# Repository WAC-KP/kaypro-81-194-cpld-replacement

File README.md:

# Kaypro 81-194 cpld replacement
Replacement for the 1984 Kaypro Universal Board 81-194 LSI using an ATF1504 CPLD, AS6C1008 SRAM and 16 mHz oscillator.

## License

This project is licensed under the **GNU General Public License v3.0 (GPLv3)**. 

### What this means for the community:
- **You are free** to download, build, modify, and use these schematics, Gerbers, and CPLD code for your own Kaypro computers.
- **You can manufacture** these replacement boards for yourself or sell them to other hobbyists.
- **CRITICAL CONDITION:** If you modify the CPLD code or the PCB layout and choose to distribute or sell your new version, **you are legally required to make your modified source code and hardware design files publicly available** under this exact same GPLv3 license. 

For the full legal text, see the accompanying `LICENSE` file.

## Why this project

A while back I purchased a nonworking Kaypro 2x as a parts computer. It was dirty and many of the screws were rusting. The keyboard jack was broken. The power supply was broken (literally). Otherwise everything else looked good. Comparison to a working 2x revealed a few bad RAM chips and the corrupted 81-194 LSI. Replacing the faulty ram and borrowing a working 81-194 resulted in a fully functional Kaypro 2X. 

A web search revealed no viable solutions to the dead LSI chip. So I asked AI for help. At the suggestion (urging) of AI and to simplify code, the design moved away from RAM to SRAM. The end result was a working, stable Kaypro 2x. 

Was it worth it? Perhaps, perhaps not. You can still find universal board Kaypros, working or not. Prototype PCBs are not too expensive until you add in shipping. Parts are reasonable but all combined you might just get lucky and find another Kaypro for less than the parts and labor.

That said, I believe it was worth it, simply based on the learning process and the side result of a functional Kaypro.

## Downloads & Project Files

Instead of hunting through folders, you can access the core design files for this project directly using the links below:

### 🛠️ Hardware & PCB Fabrication
* **Schematic Diagram:** [View or Download Schematic PDF](hardware/Version%201/u29-1504.pdf)
* **Gerber Files V1:** [Download V1 PCB Fabrication ZIP](hardware/Version%201/production/u29-1504.zip)
* **Gerber Files V2:** [Download V2 PCB Fabrication ZIP](hardware/Version%202/production/u29-1504.zip)
* *Note: The Gerber ZIP file can be uploaded directly to manufacturing services like JLCPCB, PCBWay, or OSH Park. Version 2 is just a repositioning of components.

### 💾 Firmware & Source Code
* **CPLD Source Code:** [ATF1504 PLD Source Code](firmware/KAYPRO_SRAM_CTRL-6.pld)
* **Compiled JEDEC File:** [Ready-to-Program JED file](firmware/KAYPRO_SRAM_CTRL-6.jed)
* **Compiled svf File:** [Ready-to-Program svf file](firmware/KAYPRO_SRAM_CTRL-6.svf)
* *Note: Use the `.jed` file directly with your USB Blaster and the ATF15xx ISP software to program the chip.*
* *Note: Use the `.svf` file directly with your modified USB Blaster Clone and UrJTAG or OpenOCD software to program the chip.*

---

### Brief notes

* The PCB is designed to replace both U29 (81-194) and U55 (74LS373). Separate the PCB into the two daughter boards and mount the components. The two boards are connected by a 16 wire ribbon cable.
* A single RST connection is provided (see the PCB)
* To minimize risk of socket damage only use rounded header pins designed for interfacing with DIP sockets. 
* 0805 surface mount capacitors and resistors are used to help reduce clutter and they can still be hand soldered. 
* External power pins can be used to supply the required 5v for programming the CPLD or the CPLD can be programmed with the board installed. 
* A heartbeat LED is provided as a visual indicator of functioning AFT1504.
* Remove all RAM chips. Remove U55. Remove failed 81-194 (U29)

### Compiling pld with WinCUPL II
 &emsp;cupl.exe -m1l -age -b -u PATH_TO\atmel.lib KAYPRO_SRAM_CTRL-6.pld  
 &emsp;fit1504.exe KAYPRO_SRAM_CTRL-6.tt2 -device PLCC44 -preassign keep -jtag on  

### Programming ATF1504AS with UrJtag
 &emsp;run JTAG  
  &emsp;&emsp;jtag> cable usbblaster  
  &emsp;&emsp;jtag> detect  
  &emsp;&emsp;jtag> part 0  
  &emsp;&emsp;jtag> instruction length 10  
  &emsp;&emsp;jtag> svf PATH_TO/KAYPRO_SRAM_CTRL-6.svf  
  &emsp;&emsp;&emsp;(programming may take a few minutes)

---  

### Resources
 - [USB Blaster Clone rev, C](https://www.amazon.com/dp/B07F5H5LPZ).
     - [Fixing a knockoff Altera USB Blaster that never worked](https://www.downtowndougbrown.com/2024/06/fixing-a-knockoff-altera-usb-blaster-that-never-worked/)
     - [Firmware binary file](https://github.com/dsm/USB-Blaster_CH552)
     - [WCHISPStudio](https://www.wch-ic.com/download/file?id=196)
 - [Microchip WinCUPL Product Page](https://www.microchip.com/en-us/development-tool/wincupl)
 - [ATMISP 7.3.1 Download (ZIP)](https://ww1.microchip.com/downloads/aemDocuments/documents/MPD/SoftwareLibrary/ATMISP_v7_3_1.zip)
 - [UrJTAG](https://urjtag.sourceforge.io/)
 - [OpenOCD](https://openocd.org/)

 <br>

Prototype Installed - forgive the oversized cable connectors. Rubber spacers stabilize the boards when cover installed.

<br><br>

## ⚠️ Kaypro Hardware & Installation Disclaimer

**CRITICAL WARNING:** This project involves modifying vintage computing equipment by directly interfacing with IC sockets. Incorrect installation or software faults can permanently destroy period-hard-to-find chips and logic boards. Use this software and hardware at your own risk.

In addition to the terms outlined in the GNU General Public License v3.0 (GPL-3.0):

* **Socket Interfacing Risk:** This software/hardware is designed to interface specifically with DIP sockets **U29** and **U55** on the **Kaypro Universal Board**. You assume all risk for incorrect orientation, bent pins, misaligned rows, or plugging into incorrect IC locations.
* **Electrical & Component Damage:** The authors and contributors shall not be held liable for any direct or indirect damage to your Kaypro mainboard, power supply (including original astec/riffa capacitors), CRT circuitry, or vintage components resulting from data corruption, improper timing signals, or logic states generated by this software.
* **Verification Required:** Ensure your board layout matches the Kaypro Universal Board configuration (e.g., Kaypro 2X, 4/84, 10) and verify all voltages before powering on the machine with this modification installed.

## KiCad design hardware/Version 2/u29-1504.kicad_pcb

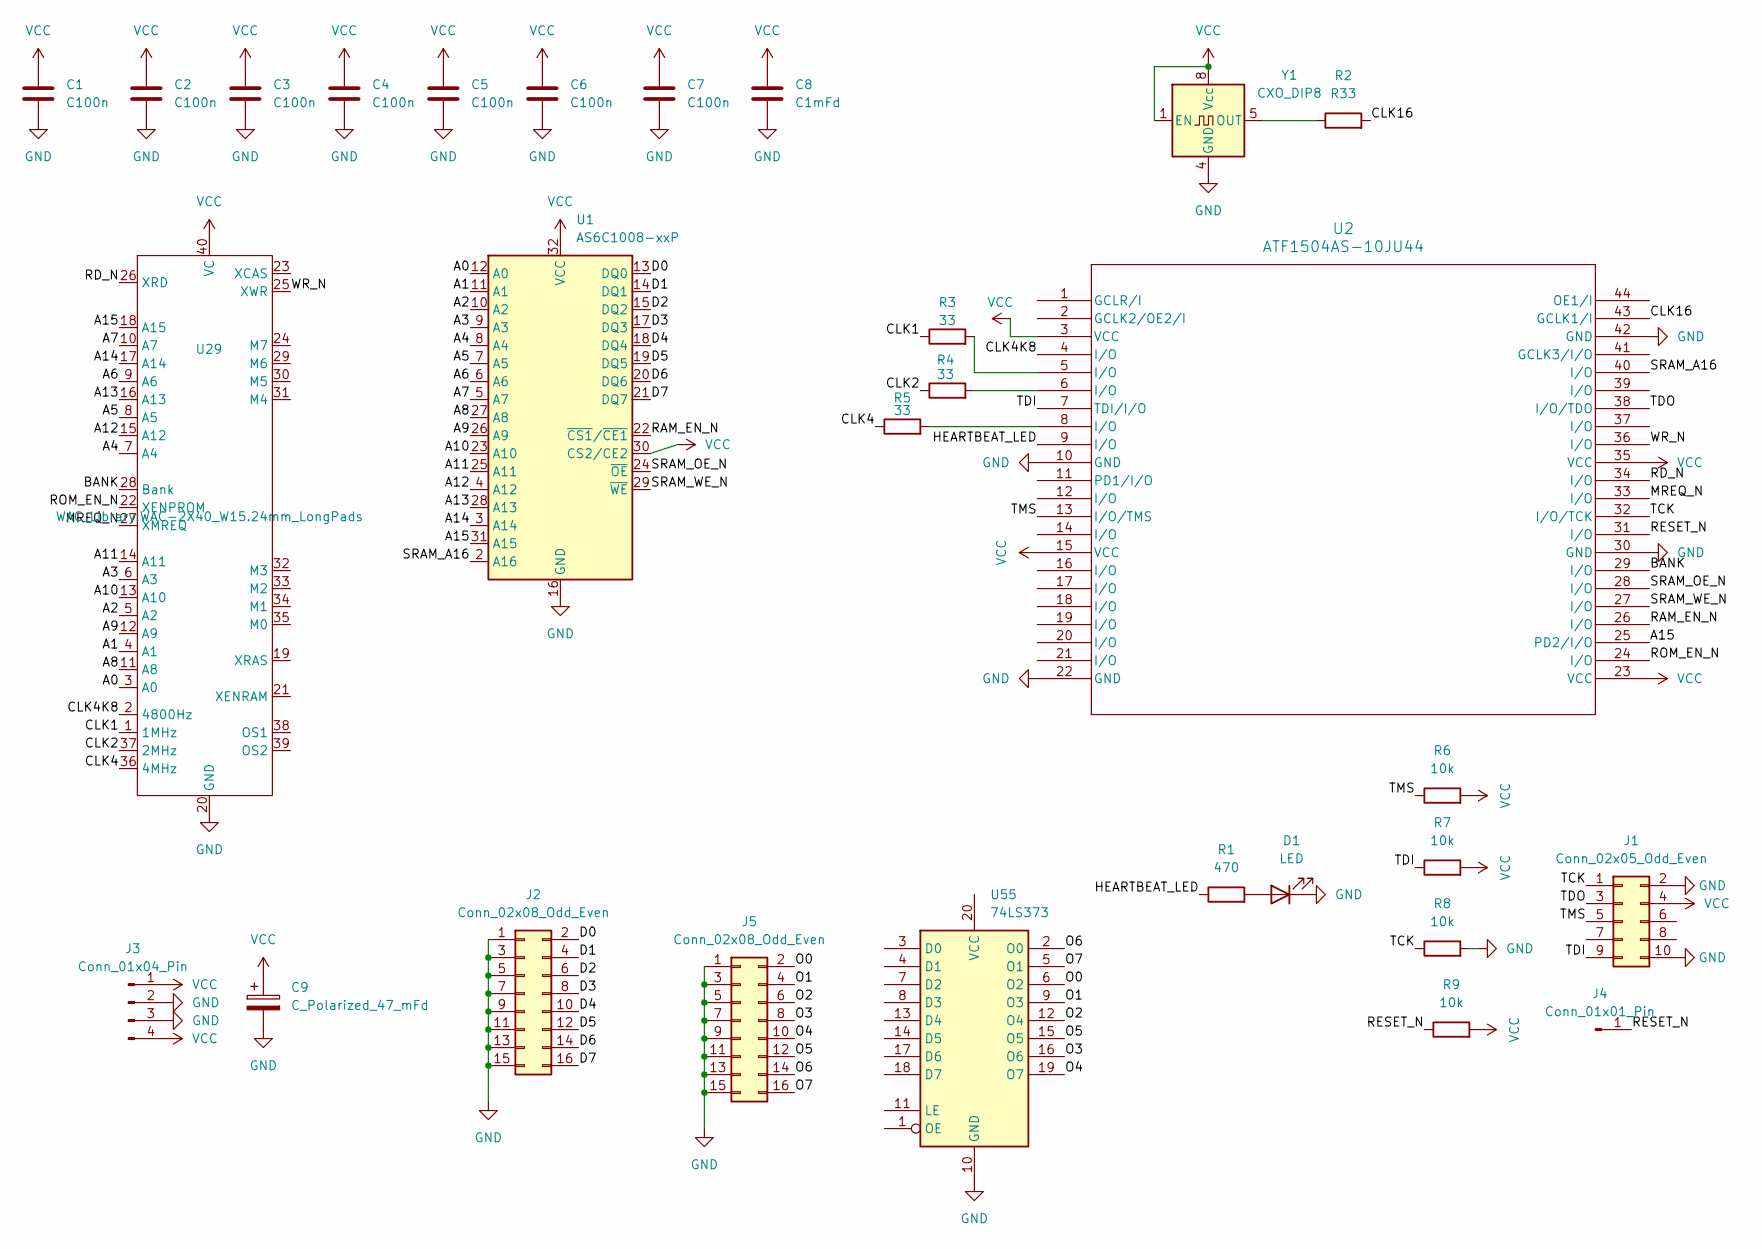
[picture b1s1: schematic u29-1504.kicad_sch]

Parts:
C1, C2, C3, C4, C5, C6, C7: C100n; C_0805_2012Metric_Pad1.18x1.45mm_HandSolder
C8: C1mFd; C_0805_2012Metric_Pad1.18x1.45mm_HandSolder
C9: C_Polarized_47_mFd; CP_Radial_D5.0mm_P2.00mm
D1: LED; LED_D3.0mm
J1: Conn_02x05_Odd_Even; IDC-Header_2x05_P2.54mm_Vertical
J2, J5: Conn_02x08_Odd_Even; PinHeader_2x08_P2.54mm_Vertical
J3: Conn_01x04_Pin; PinHeader_1x04_P2.54mm_Vertical
J4: Conn_01x01_Pin; PinHeader_1x01_P2.54mm_Vertical
R1: 470; R_0805_2012Metric_Pad1.20x1.40mm_HandSolder
R2: R33; R_0805_2012Metric_Pad1.20x1.40mm_HandSolder
R3, R4, R5: 33; R_0805_2012Metric_Pad1.20x1.40mm_HandSolder
R6, R7, R8, R9: 10k; R_0805_2012Metric_Pad1.20x1.40mm_HandSolder
U1: AS6C1008-xxP; DIP-32_W15.24mm
U2: ATF1504AS-10JU44; PLCC-44_THT-Socket
U29: Replacemnt; WAC-2X40_W15.24mm_LongPads
U55: 74LS373; DIP-20_W7.62mm
Y1: CXO_DIP8; Oscillator_DIP-8

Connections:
/A0: U1.12 (A0), U29.3 (A0)
/A1: U1.11 (A1), U29.4 (A1)
/A2: U1.10 (A2), U29.5 (A2)
/A3: U1.9 (A3), U29.6 (A3)
/A4: U1.8 (A4), U29.7 (A4)
/A5: U1.7 (A5), U29.8 (A5)
/A6: U1.6 (A6), U29.9 (A6)
/A7: U1.5 (A7), U29.10 (A7)
/A8: U1.27 (A8), U29.11 (A8)
/A9: U1.26 (A9), U29.12 (A9)
/A10: U1.23 (A10), U29.13 (A10)
/A11: U1.25 (A11), U29.14 (A11)
/A12: U1.4 (A12), U29.15 (A12)
/A13: U1.28 (A13), U29.16 (A13)
/A14: U1.3 (A14), U29.17 (A14)
/A15: U1.31 (A15), U2.25 (PD2/I/O), U29.18 (A15)
/BANK: U2.29 (I/O), U29.28 (Bank)
/CLK1: R3.1, U29.1 (1MHz)
/CLK2: R4.1, U29.37 (2MHz)
/CLK4: R5.1, U29.36 (4MHz)
/CLK4K8: U2.4 (I/O), U29.2 (4800Hz)
/CLK16: R2.2, U2.43 (GCLK1/I)
/D0: J2.2, U1.13 (DQ0)
/D1: J2.4, U1.14 (DQ1)
/D2: J2.6, U1.15 (DQ2)
/D3: J2.8, U1.17 (DQ3)
/D4: J2.10, U1.18 (DQ4)
/D5: J2.12, U1.19 (DQ5)
/D6: J2.14, U1.20 (DQ6)
/D7: J2.16, U1.21 (DQ7)
/HEARTBEAT_LED: R1.1, U2.9 (I/O)
/MREQ_N: U2.33 (I/O), U29.27 (XMREQ)
/O0: J5.2, U55.6 (O2)
/O1: J5.4, U55.9 (O3)
/O2: J5.6, U55.12 (O4)
/O3: J5.8, U55.16 (O6)
/O4: J5.10, U55.19 (O7)
/O5: J5.12, U55.15 (O5)
/O6: J5.14, U55.2 (O0)
/O7: J5.16, U55.5 (O1)
/RAM_EN_N: U1.22 (~CS1/~CE1), U2.26 (I/O)
/RD_N: U2.34 (I/O), U29.26 (XRD)
/RESET_N: J4.1 (Pin_1_1), R9.1, U2.31 (I/O)
/ROM_EN_N: U2.24 (I/O), U29.22 (XENPROM)
/SRAM_A16: U1.2 (A16), U2.40 (I/O)
/SRAM_OE_N: U1.24 (~OE), U2.28 (I/O)
/SRAM_WE_N: U1.29 (~WE), U2.27 (I/O)
/TCK: J1.1, R8.1, U2.32 (I/O/TCK)
/TDI: J1.9, R7.1, U2.7 (TDI/I/O)
/TDO: J1.3, U2.38 (I/O/TDO)
/TMS: J1.5, R6.1, U2.13 (I/O/TMS)
/WR_N: U2.36 (I/O), U29.25 (XWR)
GND: C1.2, C2.2, C3.2, C4.2, C5.2, C6.2, C7.2, C8.2, C9.2, D1.1 (K), J1.2, J1.10, J2.1, J2.3, J2.5, J2.7, J2.9, J2.11, J2.13, J2.15, J3.2, J3.3, J5.1, J5.3, J5.5, J5.7, J5.9, J5.11, J5.13, J5.15, R8.2, U1.16 (GND), U2.10 (GND), U2.22 (GND), U2.30 (GND), U2.42 (GND), U29.20 (GND), U55.10 (GND), Y1.4 (GND)
unnamed: D1.2 (A), R1.2
unnamed: R3.2, U2.5 (I/O)
unnamed: R4.2, U2.6 (I/O)
unnamed: R5.2, U2.8 (I/O)
unnamed: R2.1, Y1.5 (OUT)
VCC: C1.1, C2.1, C3.1, C4.1, C5.1, C6.1, C7.1, C8.1, C9.1, J1.4, J3.1, J3.4, R6.2, R7.2, R9.2, U1.30 (CS2/CE2), U1.32 (VCC), U2.3 (VCC), U2.15 (VCC), U2.23 (VCC), U2.35 (VCC), U29.40 (VC), Y1.1 (EN), Y1.8 (Vcc)

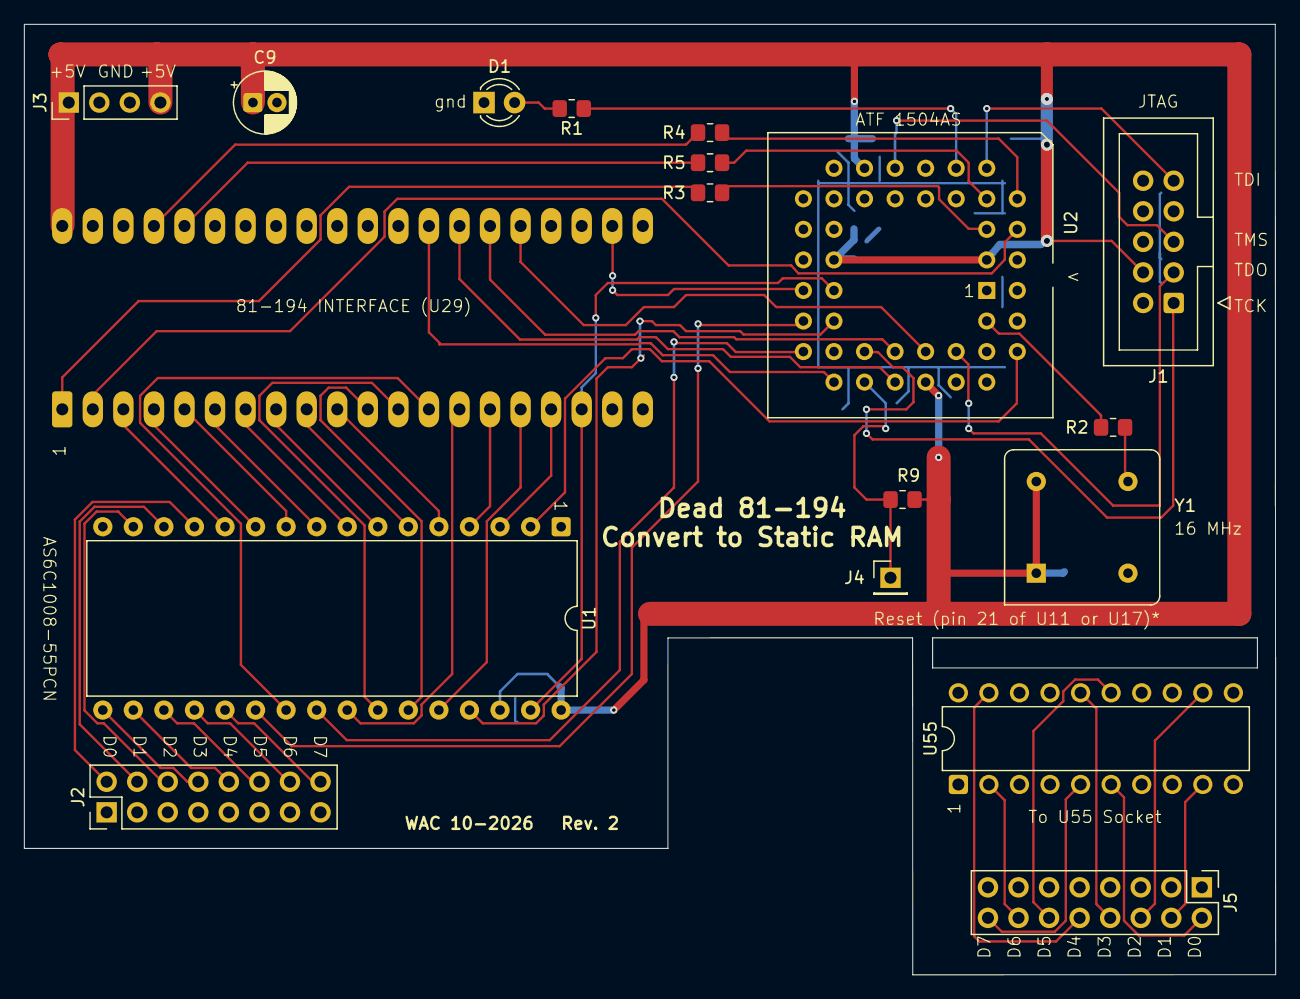
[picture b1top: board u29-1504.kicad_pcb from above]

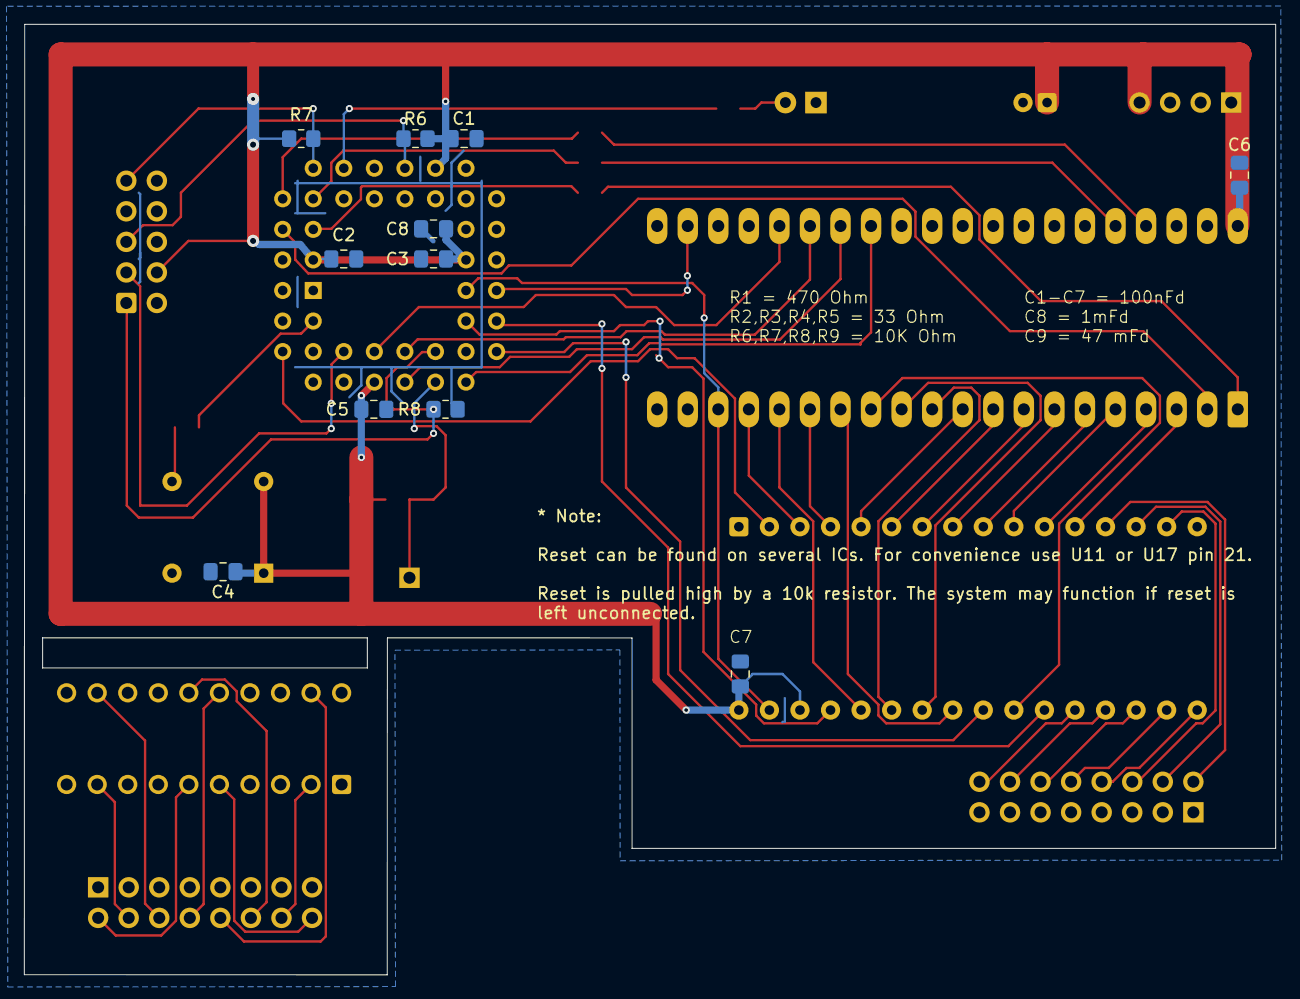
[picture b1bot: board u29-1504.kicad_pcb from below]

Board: 2 copper layers, 104.0 x 79.0 mm, 29 parts (11 on the bottom side), 59 nets.

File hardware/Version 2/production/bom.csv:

Designator,Footprint,Quantity,Value,LCSC Part #
"C1, C2, C3, C4, C5, C6, C7",0805,7,C100n,
C8,0805,1,C1mFd,
C9,CP_Radial_D5.0mm_P2.00mm,1,C_Polarized_47_mFd,
D1,LED_D3.0mm,1,LED,
J1,IDC-Header_2x05_P2.54mm_Vertical,1,Conn_02x05_Odd_Even,
"J2, J5",PinHeader_2x08_P2.54mm_Vertical,2,Conn_02x08_Odd_Even,
J3,PinHeader_1x04_P2.54mm_Vertical,1,Conn_01x04_Pin,
J4,PinHeader_1x01_P2.54mm_Vertical,1,Conn_01x01_Pin,
R1,0805,1,470,
R2,0805,1,R33,
"R3, R4, R5",0805,3,33,
"R6, R7, R8, R9",0805,4,10k,
U1,DIP-32_W15.24mm,1,AS6C1008-xxP,
U2,PLCC-44_THT-Socket,1,ATF1504AS-10JU44,
U29,WAC-2X40_W15.24mm_LongPads,1,Replacemnt,
U55,DIP-20_W7.62mm,1,74LS373,
Y1,Oscillator_DIP-8,1,CXO_DIP8,
